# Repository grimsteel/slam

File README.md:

# SLAM

EKF-SLAM on an STM32

Project progress:
- [x] SLAM implementation (theoretical)
- [x] Robot w/ lidar
- [x] Dead reckoning
- [x] Linear motion model 
- [x] Landmark detection (LiDAR)
- [ ] STM EKF filter
- [ ] STM EKF-SLAM (& landmark storage)

[Robot CAD](https://cad.onshape.com/documents/9e30bb890a60f460f17f0578/w/5d32139569da3ee478d63869/e/addadc4122316ab2e6a7443b)

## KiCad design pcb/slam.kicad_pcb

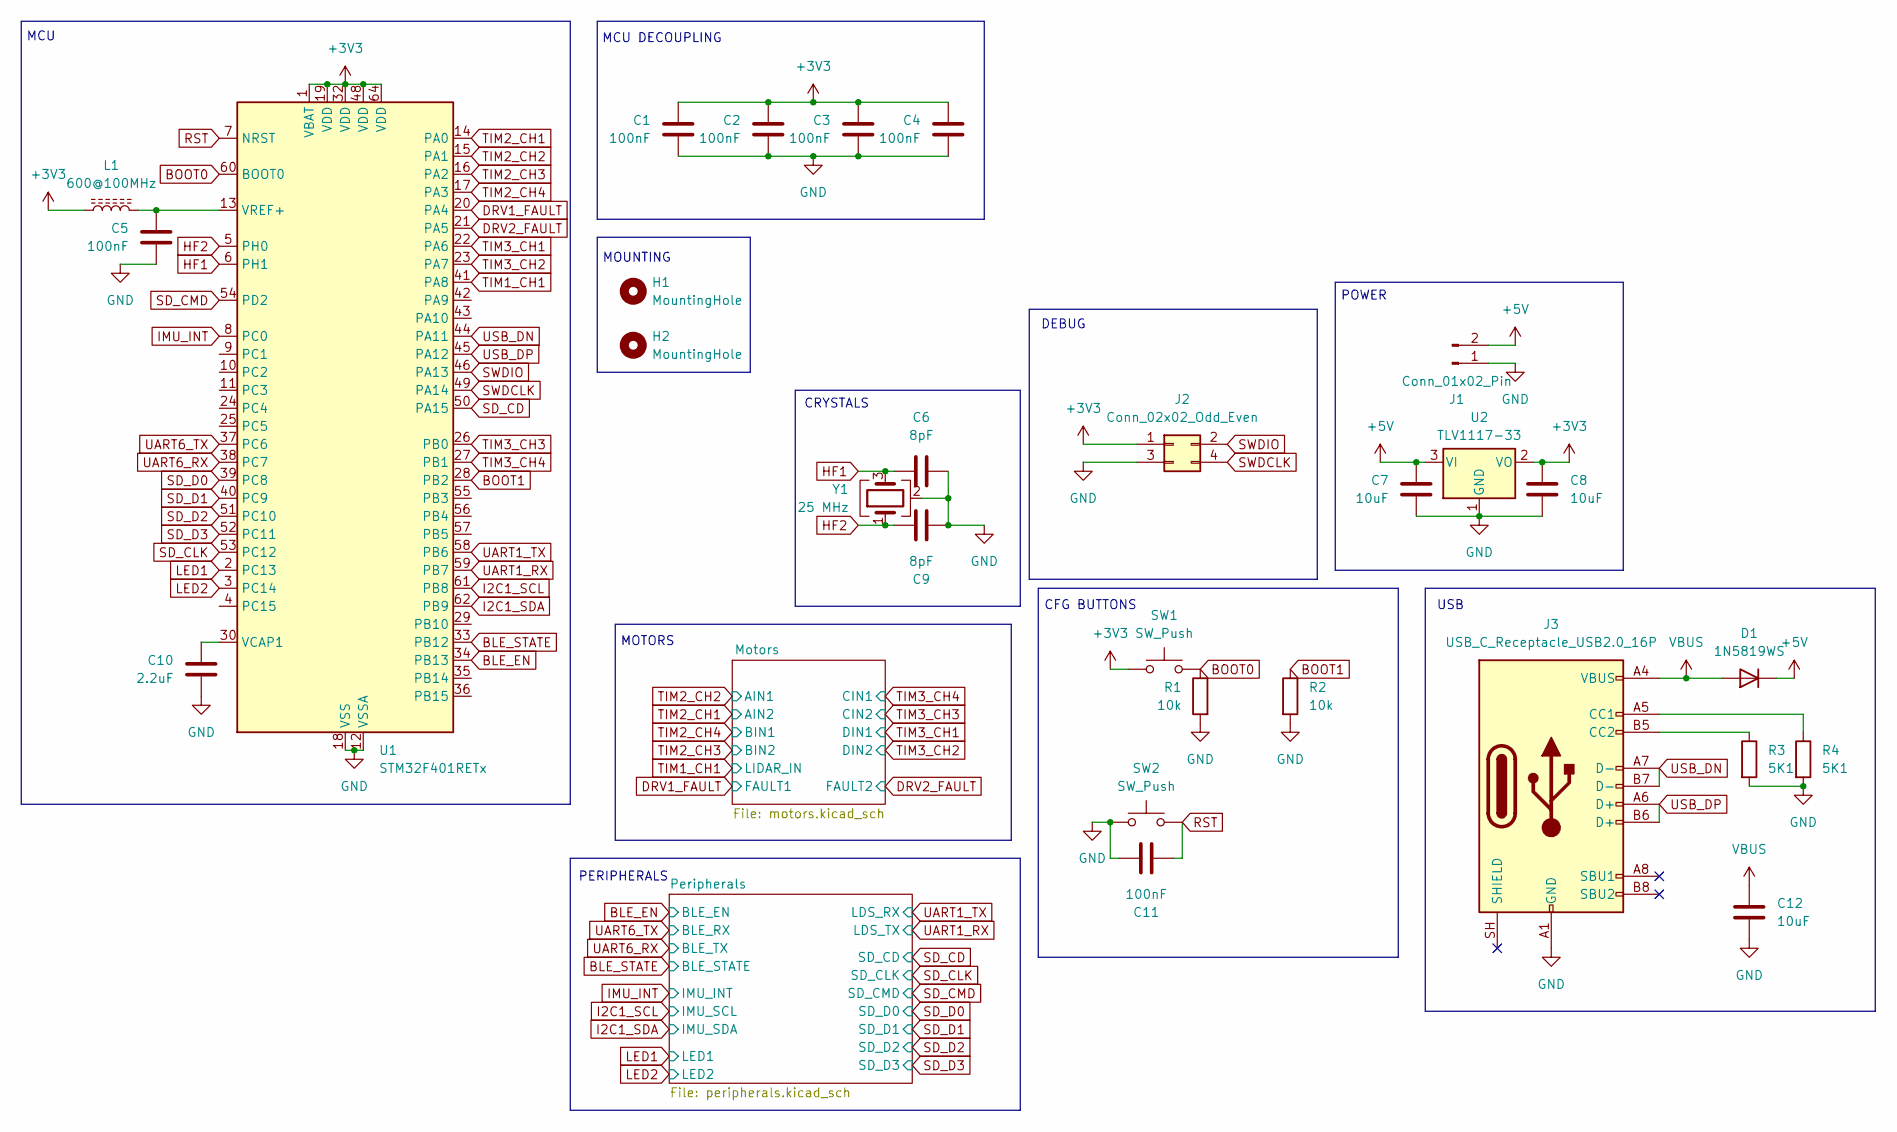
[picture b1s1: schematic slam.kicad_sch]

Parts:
C1, C2, C3, C4, C5, C11: 100nF; C_0805_2012Metric_Pad1.18x1.45mm_HandSolder; LCSC C3865954
C6, C9: 8pF; C_0603_1608Metric_Pad1.08x0.95mm_HandSolder; LCSC C53308513
C7, C8, C12: 10uF; C_0603_1608Metric_Pad1.08x0.95mm_HandSolder; LCSC C92487
C10: 2.2uF; C_0603_1608Metric_Pad1.08x0.95mm_HandSolder; LCSC C913904
D1: 1N5819WS; D_SOD-123; LCSC C8598
H1, H2: MountingHole; MountingHole_2.2mm_M2
J1: Conn_01x02_Pin; JST_PH_B2B-PH-K_1x02_P2.00mm_Vertical
J2: Conn_02x02_Odd_Even; PinHeader_2x02_P2.54mm_Vertical
J3: USB_C_Receptacle_USB2.0_16P; USB-C-SMD_SHOU_TYPE-C-16P-CB1.6; LCSC C2906290
L1: 600@100MHz; L_0603_1608Metric_Pad1.05x0.95mm_HandSolder; LCSC C133937
R1, R2: 10k; R_0805_2012Metric_Pad1.20x1.40mm_HandSolder; LCSC C2930231
R3, R4: 5K1; R_0603_1608Metric_Pad0.98x0.95mm_HandSolder; LCSC C23186
SW1, SW2: SW_Push; SW-SMD_L4.0-W2.9-LS5.0
U1: STM32F401RETx; LQFP-64_10x10mm_P0.5mm; LCSC C116978
U2: TLV1117-33; SOT-223-3_TabPin2; LCSC C48937499
Y1: 25 MHz; Crystal_SMD_3225-4Pin_3.2x2.5mm_HandSoldering; LCSC C2901684

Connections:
+3V3: C1.1, C2.1, C3.1, C4.1, C8.1, J2.1, L1.1, SW1.1, U1.1 (VBAT), U1.19 (VDD), U1.32 (VDD), U1.48 (VDD), U1.64 (VDD), U2.2 (VO); also elsewhere on the board
+5V: C7.1, D1.1 (K), J1.2, U2.3 (VI); also elsewhere on the board
BLE_EN: U1.34 (PB13); also elsewhere on the board
BLE_STATE: U1.33 (PB12); also elsewhere on the board
BOOT0: R1.1, SW1.2, U1.60 (BOOT0)
BOOT1: R2.1, U1.28 (PB2)
DRV1_FAULT: U1.20 (PA4); also elsewhere on the board
DRV2_FAULT: U1.21 (PA5); also elsewhere on the board
GND: C1.2, C2.2, C3.2, C4.2, C5.2, C6.1, C7.2, C8.2, C9.1, C10.2, C11.2, C12.2, J1.1, J2.3, J3.A1 (GND), J3.A12 (GND), J3.B1 (GND), J3.B12 (GND), R1.2, R2.2, R3.2, R4.2, SW2.1, U1.12 (VSSA), U1.18 (VSS), U1.31 (VSS), U1.47 (VSS), U1.63 (VSS), U2.1 (GND), Y1.2 (G), Y1.4 (G); also elsewhere on the board
HF1: C6.2, U1.6 (PH1), Y1.3
HF2: C9.2, U1.5 (PH0), Y1.1
I2C1_SCL: U1.61 (PB8); also elsewhere on the board
I2C1_SDA: U1.62 (PB9); also elsewhere on the board
IMU_INT: U1.8 (PC0); also elsewhere on the board
LED1: U1.2 (PC13); also elsewhere on the board
LED2: U1.3 (PC14); also elsewhere on the board
unnamed: J3.A5 (CC1), R4.1
unnamed: J3.B5 (CC2), R3.1
unnamed: C10.1, U1.30 (VCAP1)
unnamed: C5.1, L1.2, U1.13 (VREF+)
RST: C11.1, SW2.2, U1.7 (NRST)
SD_CD: U1.50 (PA15); also elsewhere on the board
SD_CLK: U1.53 (PC12); also elsewhere on the board
SD_CMD: U1.54 (PD2); also elsewhere on the board
SD_D0: U1.39 (PC8); also elsewhere on the board
SD_D1: U1.40 (PC9); also elsewhere on the board
SD_D2: U1.51 (PC10); also elsewhere on the board
SD_D3: U1.52 (PC11); also elsewhere on the board
SWDCLK: J2.4, U1.49 (PA14)
SWDIO: J2.2, U1.46 (PA13)
TIM1_CH1: U1.41 (PA8); also elsewhere on the board
TIM2_CH1: U1.14 (PA0); also elsewhere on the board
TIM2_CH2: U1.15 (PA1); also elsewhere on the board
TIM2_CH3: U1.16 (PA2); also elsewhere on the board
TIM2_CH4: U1.17 (PA3); also elsewhere on the board
TIM3_CH1: U1.22 (PA6); also elsewhere on the board
TIM3_CH2: U1.23 (PA7); also elsewhere on the board
TIM3_CH3: U1.26 (PB0); also elsewhere on the board
TIM3_CH4: U1.27 (PB1); also elsewhere on the board
UART1_RX: U1.59 (PB7); also elsewhere on the board
UART1_TX: U1.58 (PB6); also elsewhere on the board
UART6_RX: U1.38 (PC7); also elsewhere on the board
UART6_TX: U1.37 (PC6); also elsewhere on the board
USB_DN: J3.A7 (D-), J3.B7 (D-), U1.44 (PA11)
USB_DP: J3.A6 (D+), J3.B6 (D+), U1.45 (PA12)
VBUS: C12.1, D1.2 (A), J3.A4 (VBUS), J3.A9 (VBUS), J3.B4 (VBUS), J3.B9 (VBUS)

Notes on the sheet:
DEBUG
USB
CRYSTALS
PERIPHERALS
MOTORS
MOUNTING
POWER
MCU
CFG BUTTONS
MCU DECOUPLING

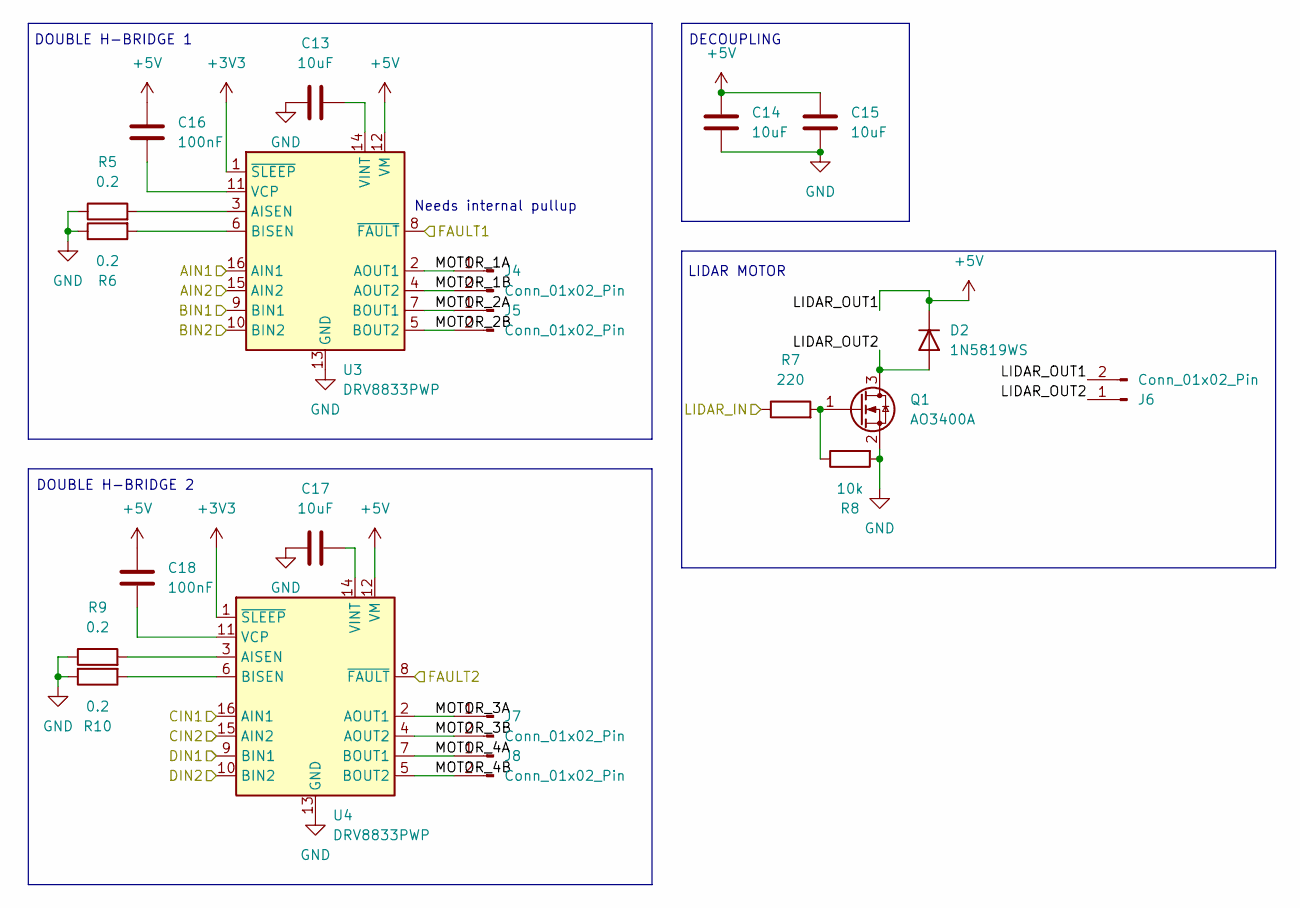
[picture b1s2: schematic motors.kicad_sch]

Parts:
C13, C14, C15, C17: 10uF; C_0603_1608Metric_Pad1.08x0.95mm_HandSolder; LCSC C92487
C16, C18: 100nF; C_0805_2012Metric_Pad1.18x1.45mm_HandSolder; LCSC C3865954
D2: 1N5819WS; D_SOD-123; LCSC C8598
J4, J5, J7, J8: Conn_01x02_Pin; SolderWire-0.15sqmm_1x02_P4mm_D0.5mm_OD1.5mm
J6: Conn_01x02_Pin; JST_PH_B2B-PH-K_1x02_P2.00mm_Vertical
Q1: AO3400A; SOT-23_Handsoldering; LCSC C347475
R5, R6, R9, R10: 0.2; R_1206_3216Metric_Pad1.30x1.75mm_HandSolder; LCSC C859989
R7: 220; R_0805_2012Metric_Pad1.20x1.40mm_HandSolder; LCSC C2933537
R8: 10k; R_0805_2012Metric_Pad1.20x1.40mm_HandSolder; LCSC C2930231
U3, U4: DRV8833PWP; HTSSOP-16-1EP_4.4x5mm_P0.65mm_EP3.4x5mm_Mask2.46x2.31mm; LCSC C50506

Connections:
+3V3: U3.1 (~SLEEP), U4.1 (~SLEEP); also elsewhere on the board
+5V: C14.2, C15.2, C16.1, C18.1, D2.1 (K), J6.2, U3.12 (VM), U4.12 (VM); also elsewhere on the board
/Motors/LIDAR_OUT2: D2.2 (A), J6.1, Q1.3 (D)
/Motors/MOTOR_1A: J4.1, U3.2 (AOUT1)
/Motors/MOTOR_1B: J4.2, U3.4 (AOUT2)
/Motors/MOTOR_2A: J5.1, U3.7 (BOUT1)
/Motors/MOTOR_2B: J5.2, U3.5 (BOUT2)
/Motors/MOTOR_3A: J7.1, U4.2 (AOUT1)
/Motors/MOTOR_3B: J7.2, U4.4 (AOUT2)
/Motors/MOTOR_4A: J8.1, U4.7 (BOUT1)
/Motors/MOTOR_4B: J8.2, U4.5 (BOUT2)
DRV1_FAULT: U3.8 (~FAULT); also elsewhere on the board
DRV2_FAULT: U4.8 (~FAULT); also elsewhere on the board
GND: C13.2, C14.1, C15.1, C17.2, Q1.2 (S), R5.1, R6.1, R8.2, R9.1, R10.1, U3.13 (GND), U3.17 (GND), U4.13 (GND), U4.17 (GND); also elsewhere on the board
unnamed: Q1.1 (G), R7.2, R8.1
unnamed: R5.2, U3.3 (AISEN)
unnamed: R6.2, U3.6 (BISEN)
unnamed: C16.2, U3.11 (VCP)
unnamed: C13.1, U3.14 (VINT)
unnamed: R9.2, U4.3 (AISEN)
unnamed: R10.2, U4.6 (BISEN)
unnamed: C18.2, U4.11 (VCP)
unnamed: C17.1, U4.14 (VINT)
TIM1_CH1: R7.1; also elsewhere on the board
TIM2_CH1: U3.15 (AIN2); also elsewhere on the board
TIM2_CH2: U3.16 (AIN1); also elsewhere on the board
TIM2_CH3: U3.10 (BIN2); also elsewhere on the board
TIM2_CH4: U3.9 (BIN1); also elsewhere on the board
TIM3_CH1: U4.9 (BIN1); also elsewhere on the board
TIM3_CH2: U4.10 (BIN2); also elsewhere on the board
TIM3_CH3: U4.15 (AIN2); also elsewhere on the board
TIM3_CH4: U4.16 (AIN1); also elsewhere on the board

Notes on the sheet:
DOUBLE H-BRIDGE 2
DECOUPLING
DOUBLE H-BRIDGE 1
LIDAR MOTOR
Needs internal pullup

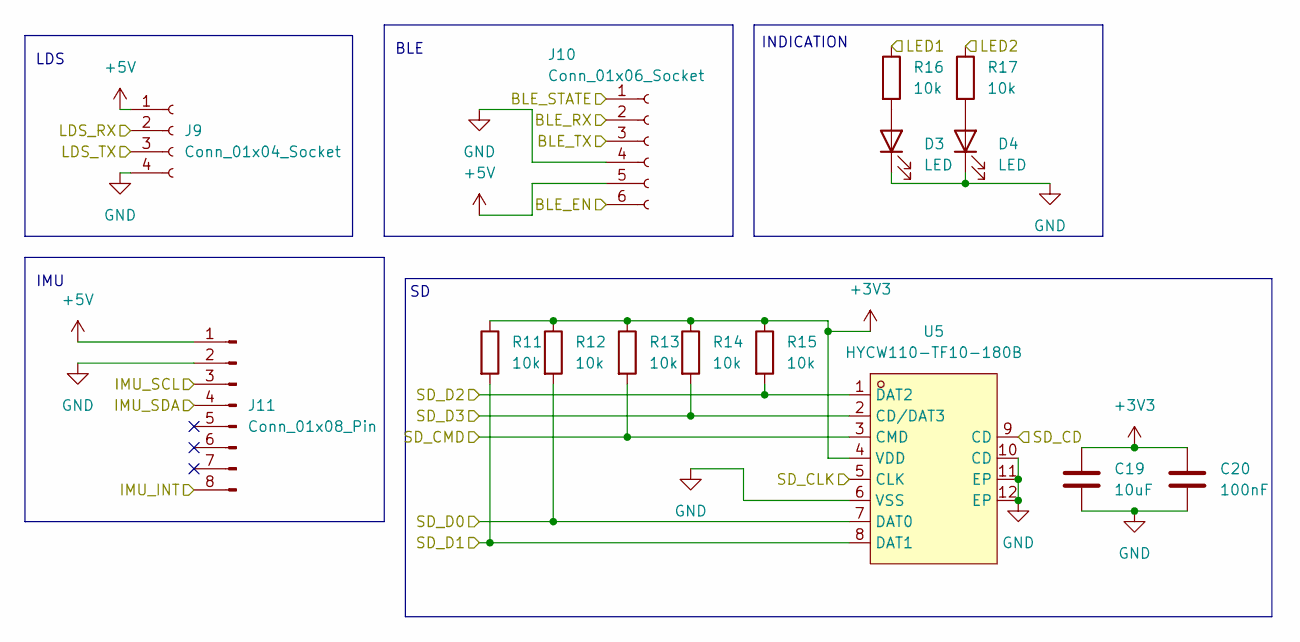
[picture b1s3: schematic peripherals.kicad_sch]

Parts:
C19: 10uF; C_0603_1608Metric_Pad1.08x0.95mm_HandSolder; LCSC C92487
C20: 100nF; C_0805_2012Metric_Pad1.18x1.45mm_HandSolder; LCSC C3865954
D3, D4: LED; LED_0805_2012Metric; LCSC C19712537
J9: Conn_01x04_Socket; JST_PH_B4B-PH-K_1x04_P2.00mm_Vertical
J10: Conn_01x06_Socket; PinSocket_1x06_P2.54mm_Vertical
J11: Conn_01x08_Pin; PinHeader_1x08_P2.54mm_Vertical
R11, R12, R13, R14, R15, R16, R17: 10k; R_0805_2012Metric_Pad1.20x1.40mm_HandSolder; LCSC C2930231
U5: HYCW110-TF10-180B; SIM-SMD_HYCW110-TF10-180B; MPN HYCW110-TF10-180B; LCSC Part C2962030

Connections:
+3V3: C19.1, C20.1, R11.1, R12.1, R13.1, R14.1, R15.1, U5.4 (VDD); also elsewhere on the board
+5V: J9.1, J10.5, J11.1; also elsewhere on the board
BLE_EN: J10.6; also elsewhere on the board
BLE_STATE: J10.1; also elsewhere on the board
GND: C19.2, C20.2, D3.1 (K), D4.1 (K), J9.4, J10.4, J11.2, U5.6 (VSS), U5.10 (CD), U5.11 (EP), U5.12 (EP); also elsewhere on the board
I2C1_SCL: J11.3; also elsewhere on the board
I2C1_SDA: J11.4; also elsewhere on the board
IMU_INT: J11.8; also elsewhere on the board
LED1: R16.1; also elsewhere on the board
LED2: R17.1; also elsewhere on the board
unnamed: D3.2 (A), R16.2
unnamed: D4.2 (A), R17.2
SD_CD: U5.9 (CD); also elsewhere on the board
SD_CLK: U5.5 (CLK); also elsewhere on the board
SD_CMD: R13.2, U5.3 (CMD); also elsewhere on the board
SD_D0: R12.2, U5.7 (DAT0); also elsewhere on the board
SD_D1: R11.2, U5.8 (DAT1); also elsewhere on the board
SD_D2: R15.2, U5.1 (DAT2); also elsewhere on the board
SD_D3: R14.2, U5.2 (CD/DAT3); also elsewhere on the board
UART1_RX: J9.3; also elsewhere on the board
UART1_TX: J9.2; also elsewhere on the board
UART6_RX: J10.3; also elsewhere on the board
UART6_TX: J10.2; also elsewhere on the board

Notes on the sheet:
IMU
LDS
INDICATION
BLE

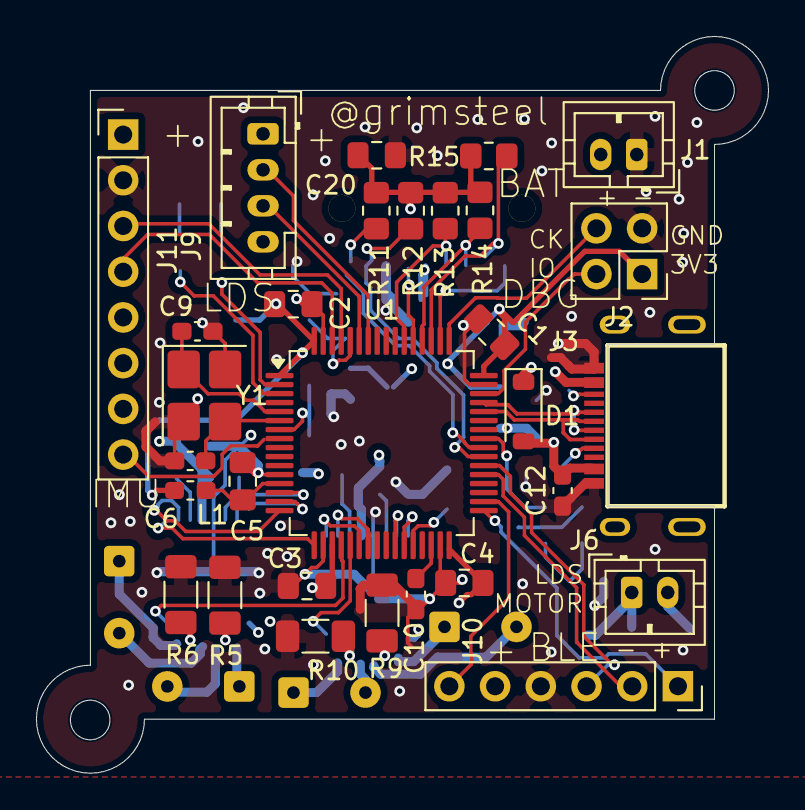
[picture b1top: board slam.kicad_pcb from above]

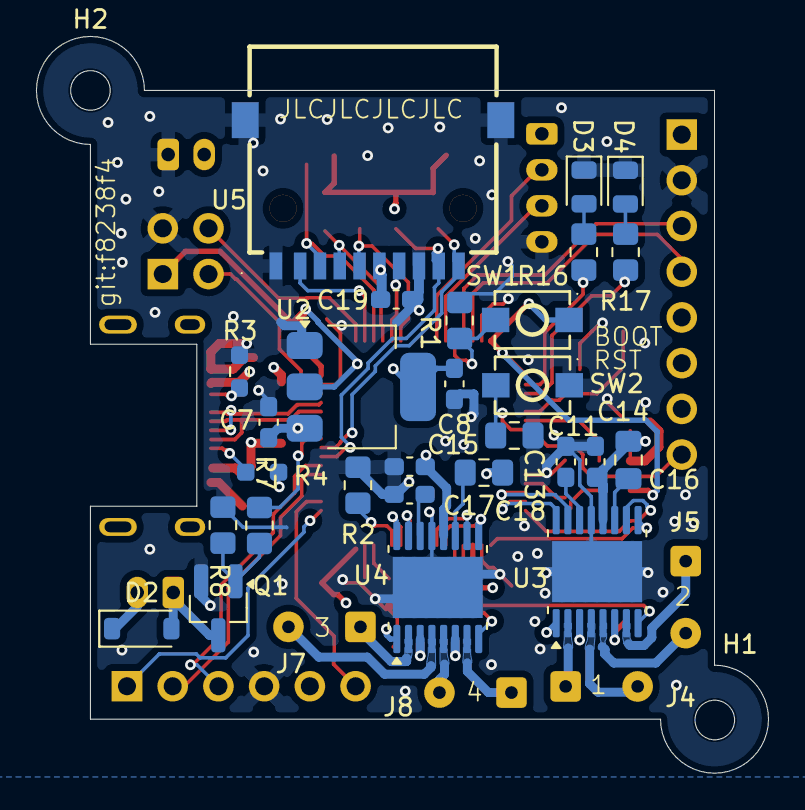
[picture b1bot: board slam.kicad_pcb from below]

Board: 4 copper layers, 40.7 x 40.9 mm, 64 parts (34 on the bottom side), 66 nets.

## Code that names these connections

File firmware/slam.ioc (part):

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Mcu.Name=STM32F401R(D-E)Tx
Mcu.Package=LQFP64
Mcu.UserName=STM32F401RETx
PA0-WKUP.Signal=S_TIM2_CH1_ETR
PA1.Signal=S_TIM2_CH2
PA11.Mode=Device_Only
PA11.Signal=USB_OTG_FS_DM
PA12.Mode=Device_Only
PA12.Signal=USB_OTG_FS_DP
PA13.Mode=Serial_Wire
PA13.Signal=SYS_JTMS-SWDIO
PA14.Mode=Serial_Wire
PA14.Signal=SYS_JTCK-SWCLK
PA15.GPIOParameters=GPIO_PuPd,GPIO_Label
PA15.GPIO_Label=SD_CD
PA15.GPIO_PuPd=GPIO_PULLUP
PA15.Signal=GPIO_Input
PA2.Signal=S_TIM2_CH3
PA3.Signal=S_TIM2_CH4
PA4.GPIOParameters=GPIO_Label
PA4.GPIO_Label=DRV1_FAULT
PA4.Signal=GPIO_Input
PA5.GPIOParameters=GPIO_Label
PA5.GPIO_Label=DRV2_FAULT
PA5.Signal=GPIO_Input
PA6.Signal=S_TIM3_CH1
PA7.Signal=S_TIM3_CH2
PA8.Signal=S_TIM1_CH1
PB0.Signal=S_TIM3_CH3
PB1.Signal=S_TIM3_CH4
PB12.GPIOParameters=GPIO_Label
PB12.GPIO_Label=BLE_STATE
PB12.Signal=GPIO_Input
PB13.GPIOParameters=GPIO_Label
PB13.GPIO_Label=BLE_EN
PB13.Signal=GPIO_Output
PB2.GPIOParameters=GPIO_Label
PB2.GPIO_Label=BOOT1
PB2.Signal=GPIO_Input
PB6.Mode=Asynchronous
PB6.Signal=USART1_TX
PB7.Mode=Asynchronous
PB7.Signal=USART1_RX
PB8.GPIOParameters=GPIO_Pu
PB8.GPIO_Pu=GPIO_PULLUP
PB8.Mode=I2C
PB8.Signal=I2C1_SCL
PB9.GPIOParameters=GPIO_Pu
PB9.GPIO_Pu=GPIO_PULLUP
PB9.Mode=I2C
PB9.Signal=I2C1_SDA
PC0.GPIOParameters=GPIO_PuPd,GPIO_Label,GPIO_ModeDefaultEXTI
PC0.GPIO_Label=IMU_INT
PC0.GPIO_ModeDefaultEXTI=GPIO_MODE_IT_FALLING
PC0.GPIO_PuPd=GPIO_PULLUP
PC0.Signal=GPXTI0
PC10.Mode=SD_4_bits_Wide_bus
PC10.Signal=SDIO_D2
PC11.Mode=SD_4_bits_Wide_bus
PC11.Signal=SDIO_D3
PC12.Mode=SD_4_bits_Wide_bus
PC12.Signal=SDIO_CK
PC13-ANTI_TAMP.GPIOParameters=GPIO_Label
PC13-ANTI_TAMP.GPIO_Label=LED2
PC13-ANTI_TAMP.Signal=GPIO_Output
PC14-OSC32_IN.GPIOParameters=GPIO_Label
PC14-OSC32_IN.GPIO_Label=LED1
PC14-OSC32_IN.Signal=GPIO_Output
PC6.Mode=Asynchronous
PC6.Signal=USART6_TX
PC7.Mode=Asynchronous
PC7.Signal=USART6_RX
PC8.Mode=SD_4_bits_Wide_bus
PC8.Signal=SDIO_D0
PC9.Mode=SD_4_bits_Wide_bus
PC9.Signal=SDIO_D1
PD2.Mode=SD_4_bits_Wide_bus
PD2.Signal=SDIO_CMD
PH0\ -\ OSC_IN.Mode=HSE-External-Oscillator
PH0\ -\ OSC_IN.Signal=RCC_OSC_IN
PH1\ -\ OSC_OUT.Mode=HSE-External-Oscillator
PH1\ -\ OSC_OUT.Signal=RCC_OSC_OUT
RCC.HSE_VALUE=25000000
RCC.SYSCLKFreq_VALUE=84000000
RCC.SYSCLKSource=RCC_SYSCLKSOURCE_PLLCLK
board=custom

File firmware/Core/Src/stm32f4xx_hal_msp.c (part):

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
    __HAL_RCC_GPIOB_CLK_ENABLE();
    /**I2C1 GPIO Configuration
    PB8     ------> I2C1_SCL
    PB9     ------> I2C1_SDA
    */
    GPIO_InitStruct.Pin = GPIO_PIN_8|GPIO_PIN_9;
    GPIO_InitStruct.Mode = GPIO_MODE_AF_OD;
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    __HAL_RCC_I2C1_CLK_DISABLE();

    /**I2C1 GPIO Configuration
    PB8     ------> I2C1_SCL
    PB9     ------> I2C1_SDA
    */
    HAL_GPIO_DeInit(GPIOB, GPIO_PIN_8);

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    __HAL_RCC_GPIOC_CLK_ENABLE();
    __HAL_RCC_GPIOD_CLK_ENABLE();
    /**SDIO GPIO Configuration
    PC8     ------> SDIO_D0
    PC9     ------> SDIO_D1
    PC10     ------> SDIO_D2
    PC11     ------> SDIO_D3
    PC12     ------> SDIO_CK
    PD2     ------> SDIO_CMD
    */
    GPIO_InitStruct.Pin = GPIO_PIN_8|GPIO_PIN_9|GPIO_PIN_10|GPIO_PIN_11
                          |GPIO_PIN_12;
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    __HAL_RCC_SDIO_CLK_DISABLE();

    /**SDIO GPIO Configuration
    PC8     ------> SDIO_D0
    PC9     ------> SDIO_D1
    PC10     ------> SDIO_D2
    PC11     ------> SDIO_D3
    PC12     ------> SDIO_CK
    PD2     ------> SDIO_CMD
    */
    HAL_GPIO_DeInit(GPIOC, GPIO_PIN_8|GPIO_PIN_9|GPIO_PIN_10|GPIO_PIN_11
                          |GPIO_PIN_12);
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    /* USER CODE END TIM1_MspPostInit 0 */
    __HAL_RCC_GPIOA_CLK_ENABLE();
    /**TIM1 GPIO Configuration
    PA8     ------> TIM1_CH1
    */
    GPIO_InitStruct.Pin = GPIO_PIN_8;
    GPIO_InitStruct.Mode = GPIO_MODE_AF_PP;
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
    __HAL_RCC_GPIOA_CLK_ENABLE();
    /**TIM2 GPIO Configuration
    PA0-WKUP     ------> TIM2_CH1
    PA1     ------> TIM2_CH2
    PA2     ------> TIM2_CH3
    PA3     ------> TIM2_CH4
    */
    GPIO_InitStruct.Pin = GPIO_PIN_0|GPIO_PIN_1|GPIO_PIN_2|GPIO_PIN_3;
    GPIO_InitStruct.Mode = GPIO_MODE_AF_PP;
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    __HAL_RCC_GPIOA_CLK_ENABLE();
    __HAL_RCC_GPIOB_CLK_ENABLE();
    /**TIM3 GPIO Configuration
    PA6     ------> TIM3_CH1
    PA7     ------> TIM3_CH2
    PB0     ------> TIM3_CH3
    PB1     ------> TIM3_CH4
    */
    GPIO_InitStruct.Pin = GPIO_PIN_6|GPIO_PIN_7;
    GPIO_InitStruct.Mode = GPIO_MODE_AF_PP;
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
    __HAL_RCC_GPIOB_CLK_ENABLE();
    /**USART1 GPIO Configuration
    PB6     ------> USART1_TX
    PB7     ------> USART1_RX
    */
    GPIO_InitStruct.Pin = GPIO_PIN_6|GPIO_PIN_7;
    GPIO_InitStruct.Mode = GPIO_MODE_AF_PP;
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
    __HAL_RCC_GPIOC_CLK_ENABLE();
    /**USART6 GPIO Configuration
    PC6     ------> USART6_TX
    PC7     ------> USART6_RX
    */
    GPIO_InitStruct.Pin = GPIO_PIN_6|GPIO_PIN_7;
    GPIO_InitStruct.Mode = GPIO_MODE_AF_PP;
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    __HAL_RCC_USART1_CLK_DISABLE();

    /**USART1 GPIO Configuration
    PB6     ------> USART1_TX
    PB7     ------> USART1_RX
    */
    HAL_GPIO_DeInit(GPIOB, GPIO_PIN_6|GPIO_PIN_7);

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    __HAL_RCC_USART6_CLK_DISABLE();

    /**USART6 GPIO Configuration
    PC6     ------> USART6_TX
    PC7     ------> USART6_RX
    */
    HAL_GPIO_DeInit(GPIOC, GPIO_PIN_6|GPIO_PIN_7);

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
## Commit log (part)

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2026-06-30 Add pcb
2026-06-30 update diode, usb routing

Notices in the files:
firmware/Core/Src/stm32f4xx_hal_msp.c:
Copyright (c) 2026 STMicroelectronics.
All rights reserved.
This software is licensed under terms that can be found in the LICENSE file
